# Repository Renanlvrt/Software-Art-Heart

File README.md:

# Artificial Heart Testing Platform

> Web-based testing platform for artificial heart prototype components

## Quick Start

### Prerequisites
- Node.js 18+ 
- npm 9+

### Installation

```bash
cd backend
npm install
```

### Run Development Server

```bash
npm run dev
```

Server starts at `http://localhost:4000`

### API Endpoints

| Method | Endpoint | Description |
|--------|----------|-------------|
| GET | `/api/health` | System status and health check |
| GET | `/api/logs` | Retrieve sensor readings |
| POST | `/api/logs` | Add a sensor reading |
| GET | `/api/logs/latest` | Get latest reading per sensor |
| GET | `/api/export` | Download readings as CSV |
| POST | `/api/control` | Send motor command |
| POST | `/api/control/emergency-stop` | Emergency stop all motors |
| GET | `/api/control/state` | Get current motor state |
| GET | `/api/control/history` | Get command history |

### WebSocket Events

**Server → Client:**
- `reading` - New sensor reading
- `state` - Motor state update
- `emergency_stop` - Emergency stop triggered

**Client → Server:**
- `control` - Send control command

## Project Structure

```
software/
├── ARCHITECTURE.md          # System design document
├── IMPLEMENTATION_LOG.md    # Development progress
├── backend/
│   ├── server.js            # Express + Socket.io server
│   ├── api/                 # REST API routes
│   ├── database/            # SQLite schema and queries
│   ├── hardware/            # Simulator and serial bridge
│   ├── services/            # Business logic
│   ├── middleware/          # Express middleware
│   └── utils/               # Validators and helpers
├── frontend/                # Web UI (coming soon)
└── docs/                    # Documentation
```

## Development

### Run Tests
```bash
npm test
```

### Run with Watch Mode
```bash
npm run dev
```

### Check Health
```bash
curl http://localhost:4000/api/health
```

## License

MIT

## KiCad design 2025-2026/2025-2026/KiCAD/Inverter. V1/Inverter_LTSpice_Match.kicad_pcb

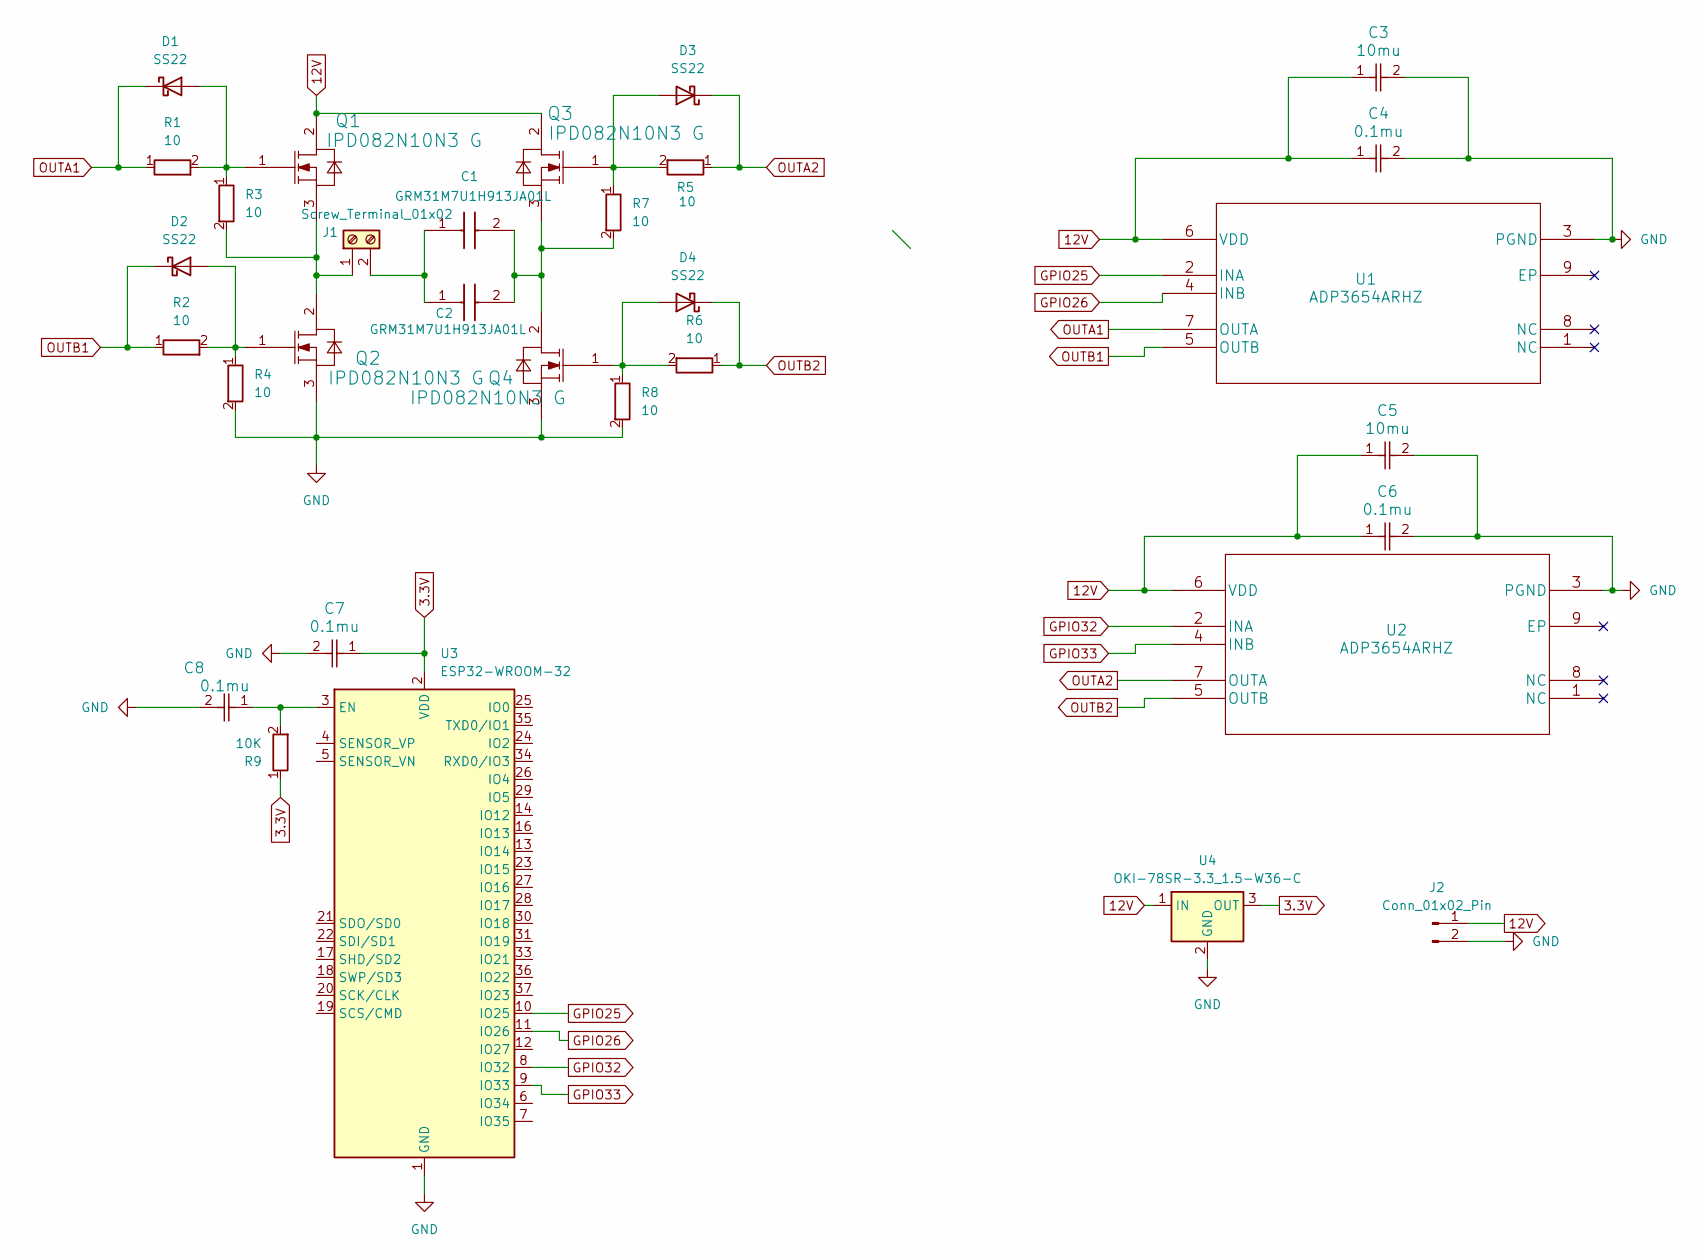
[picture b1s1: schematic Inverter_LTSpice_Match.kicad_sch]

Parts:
C1, C2: GRM31M7U1H913JA01L; c0.091mu; Manufacturer_Part_Number GRM31M7U1H913JA01L
C3, C5: 10mu; c10mu
C4, C6, C7, C8: 0.1mu; c0.1mu
D1, D2, D3, D4: SS22; D_SMA
J1: Screw_Terminal_01x02; TerminalBlock_Altech_AK300-2_P5.00mm
J2: Conn_01x02_Pin; JWT_A3963_1x02_P3.96mm_Vertical
Q1, Q2, Q3, Q4: IPD082N10N3 G; nmos; ManufacturerPartNumber IPD082N10N3 G
R1, R2, R3, R4, R5, R6, R7, R8: 10; R_0201_0603Metric
R9: 10K; R_0201_0603Metric
U1, U2: ADP3654ARHZ
U3: ESP32-WROOM-32
U4: OKI-78SR-3.3_1.5-W36-C; Converter_DCDC_Murata_OKI-78SR_Vertical

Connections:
3.3V: C7.1, R9.1, U3.2 (VDD), U4.3 (OUT)
12V: C3.1, C4.1, C5.1, C6.1, J2.1, Q1.2 (DRAIN), Q3.2 (DRAIN), U1.6 (VDD), U2.6 (VDD), U4.1 (IN)
GND: C3.2, C4.2, C5.2, C6.2, C7.2, C8.2, J2.2, Q2.3 (SOURCE), Q4.3 (SOURCE), R4.2, R8.2, U1.3 (PGND), U2.3 (PGND), U3.1 (GND), U3.15 (GND), U3.38 (GND), U3.39 (GND), U4.2 (GND)
GPIO25: U1.2 (INA), U3.10 (IO25)
GPIO26: U1.4 (INB), U3.11 (IO26)
GPIO32: U2.2 (INA), U3.8 (IO32)
GPIO33: U2.4 (INB), U3.9 (IO33)
unnamed: D1.2 (A), Q1.1 (GATE), R1.2, R3.1
unnamed: D2.2 (A), Q2.1 (GATE), R2.2, R4.1
unnamed: D3.2 (A), Q3.1 (GATE), R5.2, R7.1
unnamed: D4.2 (A), Q4.1 (GATE), R6.2, R8.1
unnamed: J1.1, Q1.3 (SOURCE), Q2.2 (DRAIN), R3.2
unnamed: C1.1, C2.1, J1.2
unnamed: C1.2, C2.2, Q3.3 (SOURCE), Q4.2 (DRAIN), R7.2
unnamed: C8.1, R9.2, U3.3 (EN)
OUTA1: D1.1 (K), R1.1, U1.7 (OUTA)
OUTA2: D3.1 (K), R5.1, U2.7 (OUTA)
OUTB1: D2.1 (K), R2.1, U1.5 (OUTB)
OUTB2: D4.1 (K), R6.1, U2.5 (OUTB)

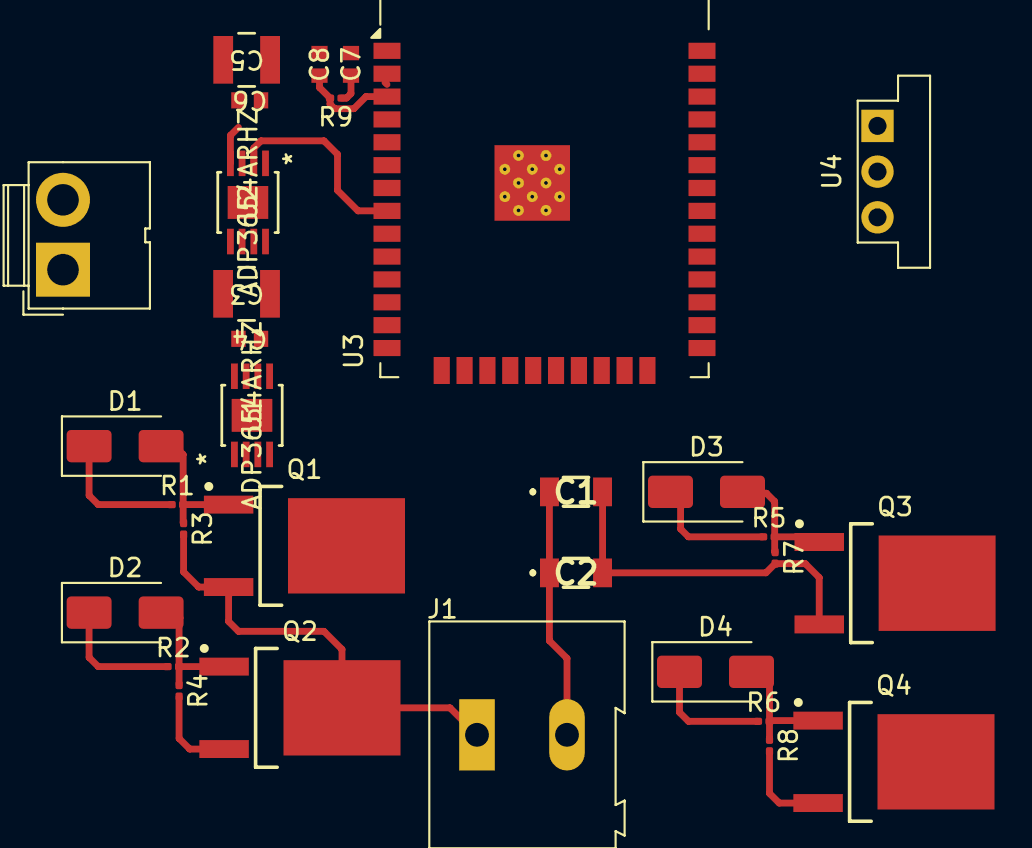
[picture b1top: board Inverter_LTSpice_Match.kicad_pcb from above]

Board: 2 copper layers, 31 parts (0 on the bottom side), 19 nets.

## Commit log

2026-01-28 creating repo for software
2026-01-28 add new file
2026-01-28 commit the prompt made
2026-01-28 trying new front-end (this one is a bit more data in the same page more control)
2026-01-28 professional design
2026-02-11 added extraction of demo database
2026-02-11 with real demoTable.db
2026-02-11 create the analysis page where we can see the whole thing again

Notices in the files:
parts and their libraries:
Copyright 2016 Accelerated Designs. All rights reserved.
